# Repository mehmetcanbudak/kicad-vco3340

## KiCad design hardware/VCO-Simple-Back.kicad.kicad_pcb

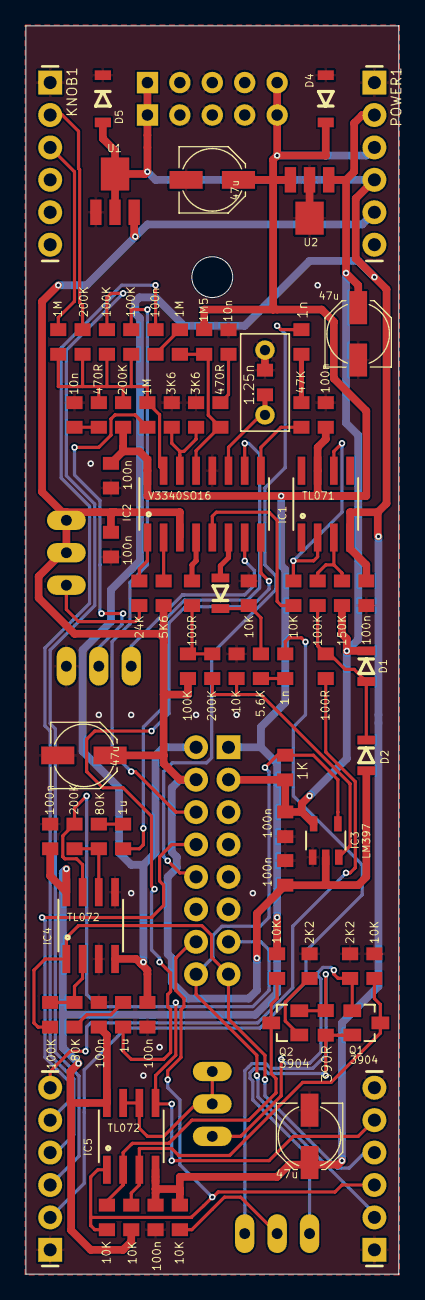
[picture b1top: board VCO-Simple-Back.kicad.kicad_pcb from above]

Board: 2 copper layers, 29.2 x 97.8 mm, 86 parts (0 on the bottom side), 56 nets.

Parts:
@HOLE0: MountingHole_3.2mm_M3
C1, C2: 1n; C-0805
C3, C10, C11, C12, C13, C14, C15, C18, C19, C21, C22: 100n; C-0805
C4, C5: 10n; C-0805
C6: 1.25n; C-0805
C7: POLY 1.250n; CAP-5MM
C8, C9: 1u; C-0805
C16, C17, C20, C23: 47u; PANASONIC_C
CTRL1: M06
D1, D2: DIODESOD-323; SOD-323
D3: D; SOD-323
D4, D5: DIODESOD-123; SOD-123
DRIVE1: POT-TRIM-MULTI-V
EXPANSION1: M08X2
HIGHFREQ1: 20K; POT-TRIM-MULTI-V
IC1: TL071; SO08
IC2: V3340SO16; SO16
IC3: LM397; SOT23-5
IC4, IC5: TL072; SO08
KNOB1: M06
OUT1: M06
P1: POWER_SIMPLE10_SHROUDED; POWER_10_SHROUDED
POWER1: M06
Q1, Q2: 3904; SOT23
R1, R22: 100R; R-0805-MILL
R2: 5.6K; R-0805-MILL
R3: 47K; R-0805-MILL
R4, R15, R16, R24, R30: 100K; R-0805-MILL
R5, R10, R27, R35, R38, R39, R41, R42: 10K; R-0805-MILL
R6: 150K; R-0805-MILL
R7, R11, R13: 1M; R-0805-MILL
R8: 1M5; R-0805-MILL
R9, R19: 470R; R-0805-MILL
R14, R18, R26, R31: 200K; R-0805-MILL
R20: 24K; R-0805-MILL
R21: 5K6; R-0805-MILL
R23, R25: 3K6; R-0805-MILL
R28, R29: 80K; R-0805-MILL
R32: 1K; R-0805-MILL
R34, R40: 2K2; R-0805-MILL
R36: 390R; R-0805-MILL
SCALE1: 10K; POT-TRIM-MULTI-V
SYMMETRY1: POT-TRIM-MULTI-V
U1: LM79L05A; SOT89
U2: MC78L05A; SOT89

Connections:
+5V: C21.1, C23.+, D1.K, EXPANSION1.3, IC3.5, POWER1.2, R6.P$1, R32.P$2, U2.1
+12V: C10.1, C12.1, C14.1, C18.1, C20.+, D4.K, EXPANSION1.1, IC1.7, IC2.16, IC4.8, IC5.8, P1.9, P1.10, POWER1.3, R8.P$2, R18.P$2, R35.P$2, R39.P$2, U2.3
-5V: C17.+, C19.2, C22.2, D2.A, EXPANSION1.4, IC2.3, IC3.2, POWER1.5, R21.P$2, R24.P$2, SCALE1.B, SCALE1.W, U1.3
-12V: C11.2, C13.2, C15.2, C16.+, D5.A, EXPANSION1.2, IC1.4, IC4.4, IC5.4, P1.1, P1.2, POWER1.4, R38.P$1, U1.2, U1.2B
/OSCILLATOR/FREQ: IC2.15, R11.P$1, R13.P$1, R14.P$1, R15.P$1, R16.P$1, R18.P$1, R19.P$2
/OSCILLATOR/HARD_SYNC_IN: D3.A, IC2.6
/OSCILLATOR/SOFT_SYNC_IN: IC2.9, R3.P$2
/POWER/PULSE-WIDTH-NORM: CTRL1.5, EXPANSION1.8
GND: C4.2, C5.2, C6.2, C7.2, C10.2, C11.1, C12.2, C13.1, C14.2, C15.1, C16.-, C17.-, C18.2, C19.1, C20.-, C21.2, C22.1, C23.-, CTRL1.1, D4.A, D5.K, EXPANSION1.5, EXPANSION1.7, EXPANSION1.9, EXPANSION1.11, HIGHFREQ1.B, IC2.12, IC3.1, IC4.3, IC4.5, KNOB1.1, OUT1.1, OUT1.6, P1.3, P1.4, P1.5, P1.6, P1.7, P1.8, POWER1.1, R5.P$2, R23.P$2, R25.P$2, R27.P$2, R34.P$1, R40.P$1, R41.P$1, U1.1, U2.2, U2.2B
LINEARFM: C3.1, CTRL1.4
unnamed: C1.2, R2.P$1
unnamed: C2.2, R3.P$1
unnamed: C3.2, R7.P$2
unnamed: C4.1, R9.P$1
unnamed: C5.1, R19.P$1
unnamed: C6.1, C7.1, IC2.11
unnamed: C8.2, R28.P$1
unnamed: C9.2, R29.P$1
unnamed: D1.A, D2.K, R1.P$2, R4.P$1
unnamed: D3.K, R2.P$2, R5.P$1
unnamed: DRIVE1.A, DRIVE1.W, IC5.6, IC5.7
unnamed: DRIVE1.B, Q1.1, R34.P$2
unnamed: HIGHFREQ1.A, IC2.7
unnamed: HIGHFREQ1.W, R11.P$2
unnamed: IC1.2, IC1.6, R10.P$2
unnamed: IC1.3, R4.P$2, R6.P$2
unnamed: IC2.1, R20.P$1
unnamed: IC2.2, R21.P$1
unnamed: IC2.4, R22.P$1
unnamed: IC2.5, R10.P$1
unnamed: IC2.13, R7.P$1, R8.P$1, R9.P$2
unnamed: IC2.14, R23.P$1, R25.P$1
unnamed: IC4.2, R28.P$2, R30.P$1
unnamed: IC4.6, R29.P$2, R31.P$1
unnamed: IC5.2, Q2.3, R39.P$1, R42.P$2
unnamed: IC5.3, Q1.3, R35.P$1, R41.P$2
unnamed: Q1.2, R36.P$1, SYMMETRY1.A
unnamed: Q2.1, R40.P$2
unnamed: Q2.2, R36.P$2, SYMMETRY1.B
unnamed: R20.P$2, SCALE1.A
unnamed: R22.P$2, R24.P$1, R26.P$1
unnamed: R38.P$2, SYMMETRY1.W
PITCH-COURSE: KNOB1.2, R14.P$2
PITCH-FINE: KNOB1.3, R13.P$2
PULSE-OUT: EXPANSION1.16, IC3.4, OUT1.2, R32.P$1
PULSE-WIDTH: CTRL1.6, R1.P$1
SAW-OUT: EXPANSION1.15, IC4.1, OUT1.4, R30.P$2
SIN-OUT: EXPANSION1.14, IC5.1, OUT1.3, R42.P$1
SOFT-SYNC: C2.1, EXPANSION1.10
SYNC: C1.1, CTRL1.2
TRI-OUT: EXPANSION1.13, IC4.7, IC5.5, OUT1.5, R31.P$2
V/OCT: CTRL1.3, R15.P$2
V/OCT-EXT: EXPANSION1.6, R16.P$2
VCO-PULSE: IC3.3, R26.P$2, R27.P$1
VCO-SAW: C8.1, IC2.8
VCO-TRI: C9.1, IC2.10

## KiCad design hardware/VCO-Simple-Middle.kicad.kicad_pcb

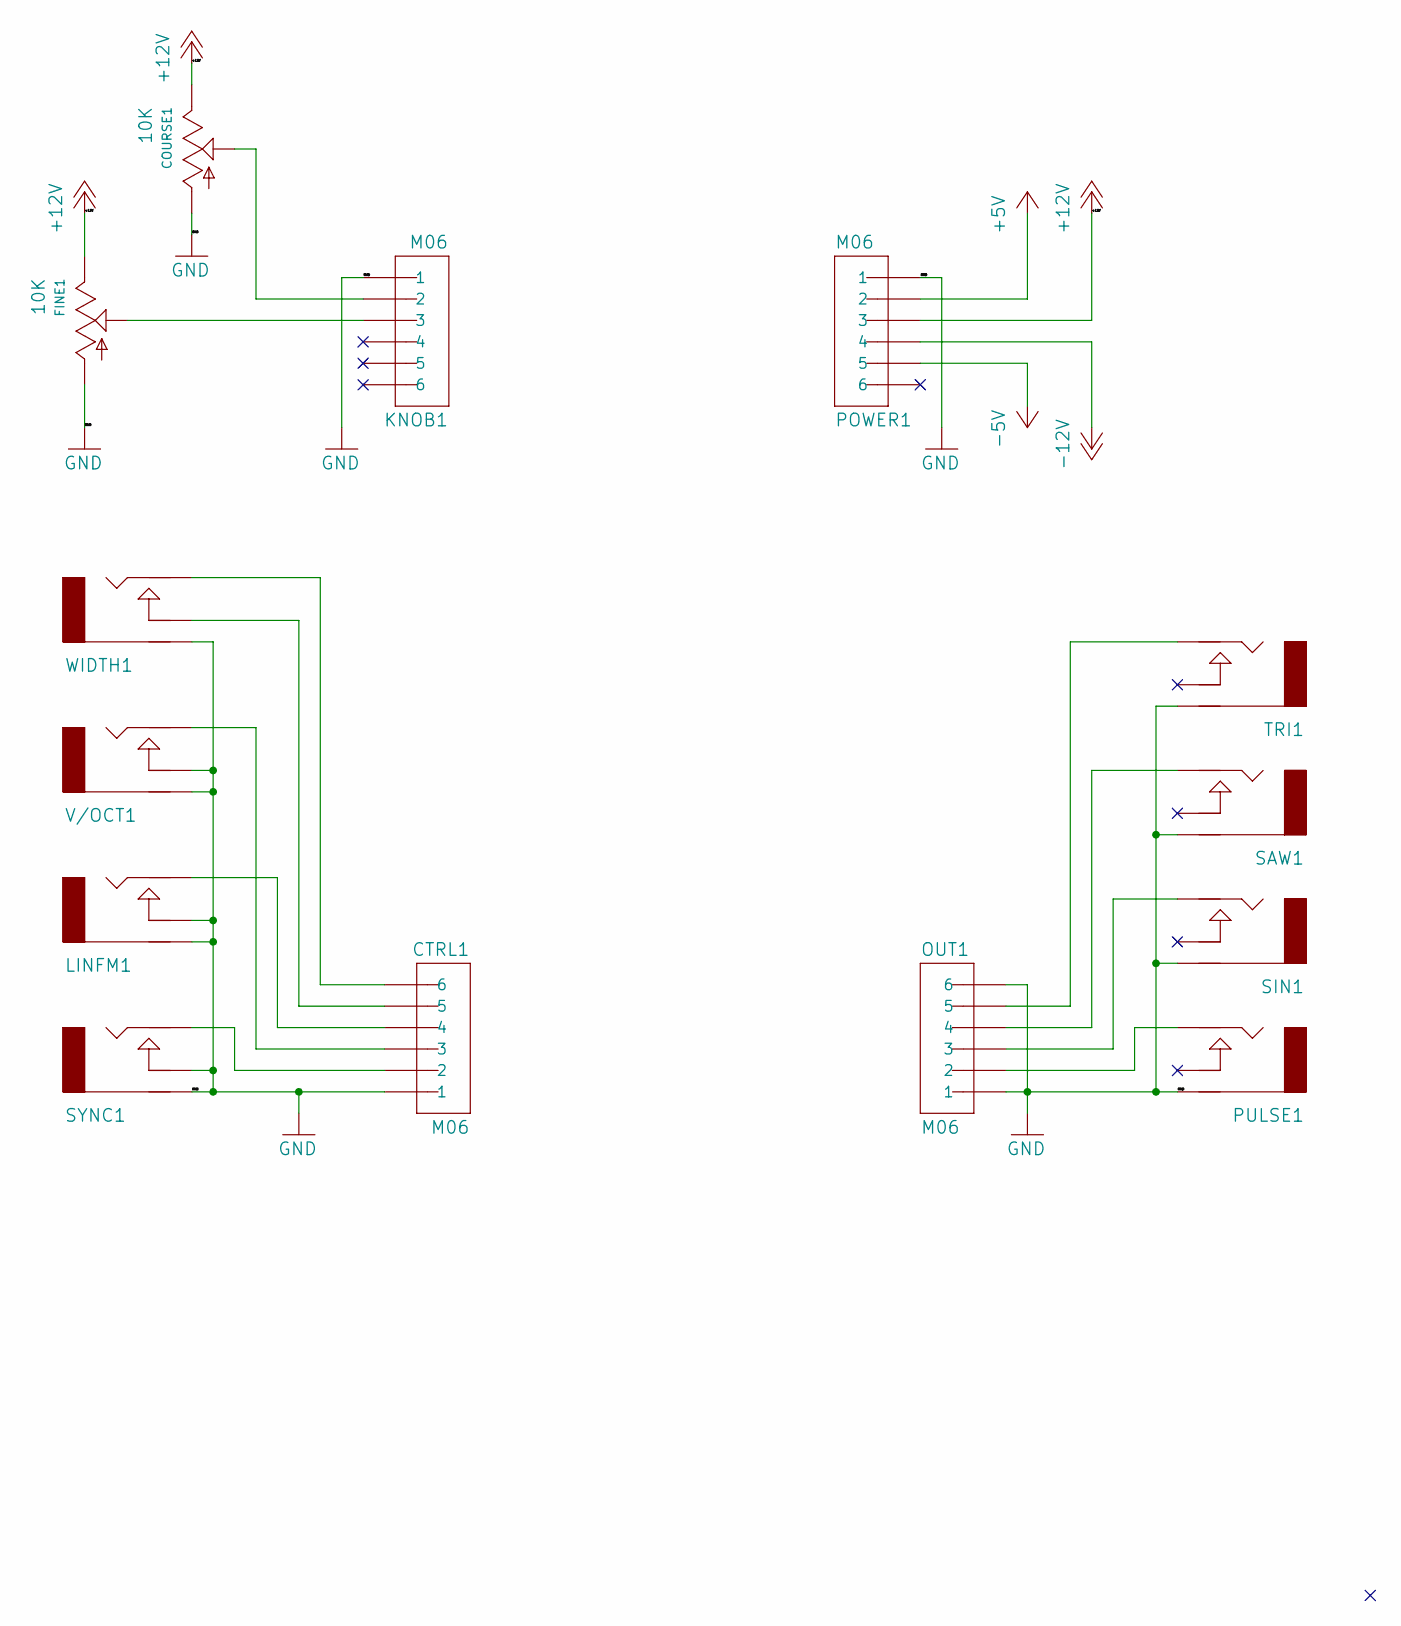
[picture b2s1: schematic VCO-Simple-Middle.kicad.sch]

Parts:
COURSE1: 10K; POT-ALPHA-9MM
CTRL1: M06
FINE1: 10K; POT-ALPHA-9MM
KNOB1: M06
LINFM1: AUDIO-JACKINLINE; ERTHENVAR-JACK-INLINE
OUT1: M06
POWER1: M06
PULSE1: AUDIO-JACKINLINE; ERTHENVAR-JACK-INLINE
SAW1: AUDIO-JACKINLINE; ERTHENVAR-JACK-INLINE
SIN1: AUDIO-JACKINLINE; ERTHENVAR-JACK-INLINE
SYNC1: AUDIO-JACKINLINE; ERTHENVAR-JACK-INLINE
TRI1: AUDIO-JACKINLINE; ERTHENVAR-JACK-INLINE
V/OCT1: AUDIO-JACKINLINE; ERTHENVAR-JACK-INLINE
WIDTH1: AUDIO-JACKINLINE; ERTHENVAR-JACK-INLINE

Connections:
+5V: POWER1.2
+12V: COURSE1.B (E), FINE1.B (E), POWER1.3
-5V: POWER1.5
-12V: POWER1.4
GND: COURSE1.A, CTRL1.1, FINE1.A, KNOB1.1, LINFM1.G (RING), LINFM1.N (NORM), OUT1.1, OUT1.6, POWER1.1, PULSE1.G (RING), SAW1.G (RING), SIN1.G (RING), SYNC1.G (RING), SYNC1.N (NORM), TRI1.G (RING), V/OCT1.G (RING), V/OCT1.N (NORM), WIDTH1.G (RING)
unnamed: COURSE1.W (S), KNOB1.2
unnamed: CTRL1.2, SYNC1.T (TIP)
unnamed: CTRL1.3, V/OCT1.T (TIP)
unnamed: CTRL1.4, LINFM1.T (TIP)
unnamed: CTRL1.5, WIDTH1.N (NORM)
unnamed: CTRL1.6, WIDTH1.T (TIP)
unnamed: FINE1.W (S), KNOB1.3
unnamed: OUT1.2, PULSE1.T (TIP)
unnamed: OUT1.3, SIN1.T (TIP)
unnamed: OUT1.4, SAW1.T (TIP)
unnamed: OUT1.5, TRI1.T (TIP)

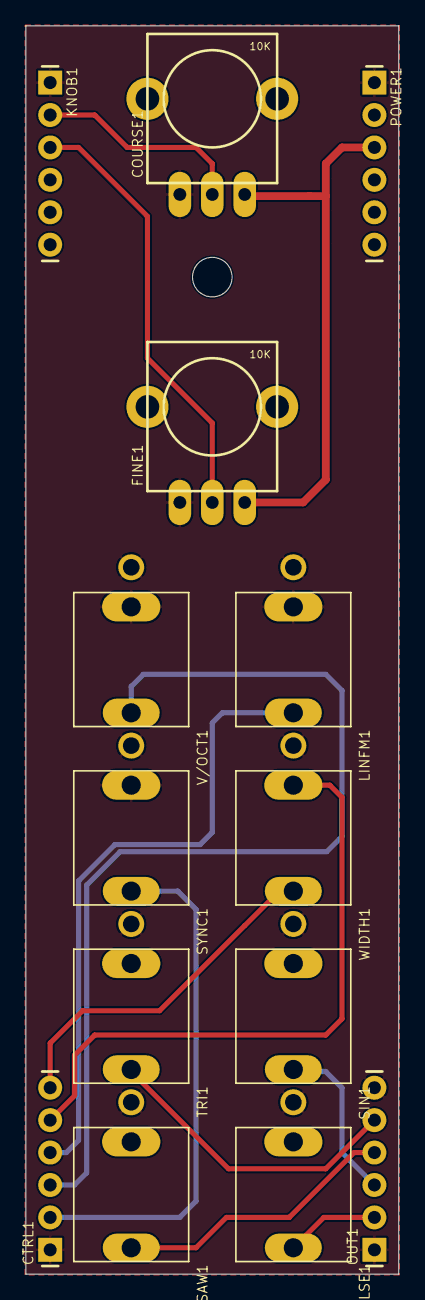
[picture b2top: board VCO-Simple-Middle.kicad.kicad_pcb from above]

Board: 2 copper layers, 29.2 x 97.8 mm, 15 parts (0 on the bottom side), 13 nets.

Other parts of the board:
@HOLE0: (no value)

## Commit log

2020-11-15 convert to kicad
2020-11-15 silkscreen: move values to f-silk, added 3d models to footprints
2020-11-15 move boards to their own folder
2020-11-15 gerbers and panel
2020-11-15 panel updates
